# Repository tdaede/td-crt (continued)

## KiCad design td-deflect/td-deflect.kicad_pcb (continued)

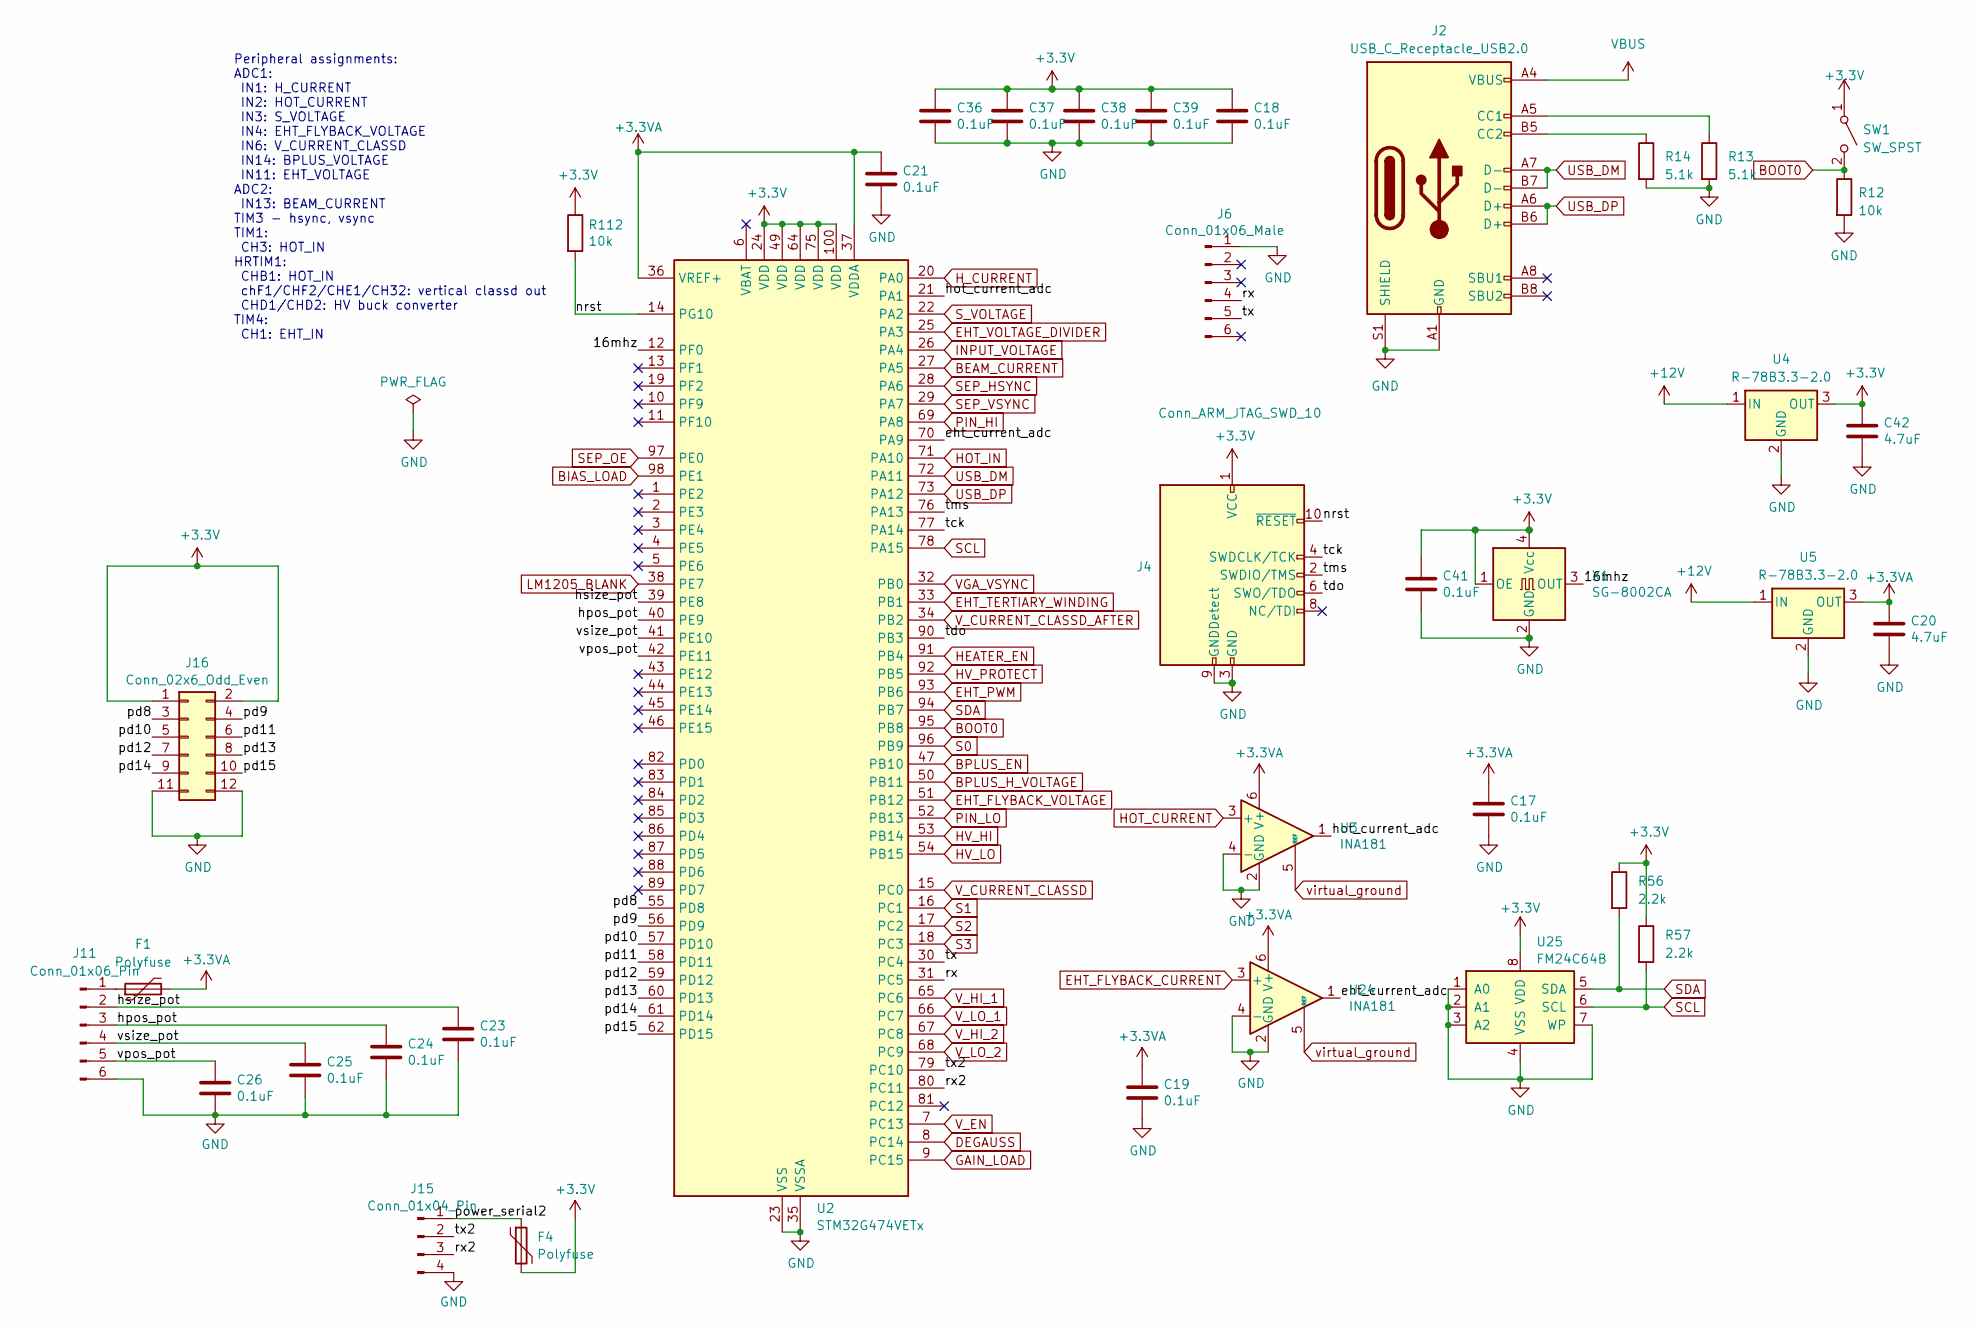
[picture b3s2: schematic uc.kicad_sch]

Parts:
C17, C18, C19, C21, C23, C24, C25, C26, C36, C37, C38, C39, C41: 0.1uF; C_0805_2012Metric_Pad1.18x1.45mm_HandSolder; Voltage 10V; Digikey 311-1140-1-ND
C20, C42: 4.7uF; C_1206_3216Metric; Voltage 10V; Digikey 1276-3177-1-ND
F1: Polyfuse; Fuse_0805_2012Metric; Digikey 507-1801-1-ND
F4: Polyfuse; Fuse_1206_3216Metric; Digikey 507-1801-1-ND
J2: USB_C_Receptacle_USB2.0; USB_C_Receptacle_XKB_U262-16XN-4BVC11; Digikey 2073-USB4105-GF-ACT-ND
J4: Conn_ARM_JTAG_SWD_10; PinHeader_2x05_P1.27mm_Vertical_SMD; Digikey SAM9438-ND
J6: Conn_01x06_Male; PinHeader_1x06_P2.54mm_Vertical; Digikey DNP
J11: Conn_01x06_Pin; JST_XH_B6B-XH-A_1x06_P2.50mm_Vertical; Digikey 455-B6B-XH-A-ND
J15: Conn_01x04_Pin; JST_XH_B4B-XH-A_1x04_P2.50mm_Vertical; Digikey 455-B4B-XH-A-ND
J16: Conn_02x6_Odd_Even; IDC-Header_2x06_P2.54mm_Vertical; Digikey 2057-BHR-12-VUA-ND
R12: 10k; R_0805_2012Metric; Digikey 311-10.0KCRCT-ND
R13, R14: 5.1k; R_0805_2012Metric; Digikey 311-5.10KCRCT-ND
R56, R57: 2.2k; R_0805_2012Metric; Digikey 311-2.20KCRCT-ND
R112: 10k; R_0805_2012Metric_Pad1.20x1.40mm_HandSolder; Digikey 311-10.0KCRCT-ND
SW1: SW_SPST; SW_DPDT_CK_JS202011JCQN; Digikey CKN10723CT-ND
U2: STM32G474VETx; LQFP-100_14x14mm_P0.5mm; Digikey 497-19476-ND
U3, U24: INA181; SOT-23-6; Digikey 296-47658-1-ND
U4, U5: R-78B3.3-2.0; Converter_DCDC_RECOM_R-78B-2.0_THT; Digikey 945-3040-ND
U25: FM24C64B; SOIC-8_3.9x4.9mm_P1.27mm; Digikey 448-FM24C64B-GTRCT-ND
X1: SG-8002CA; Oscillator_SMD_SeikoEpson_SG8002CA-4Pin_7.0x5.0mm; Digikey CTX270LVCT-ND

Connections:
+3.3V: C18.1, C36.1, C37.1, C38.1, C39.1, C41.1, C42.1, F4.2, J4.1 (VCC), J16.1, J16.2, R56.1, R57.1, R112.1, SW1.1 (A), U2.24 (VDD), U2.49 (VDD), U2.64 (VDD), U2.75 (VDD), U2.100 (VDD), U4.3 (OUT), U25.8 (VDD), X1.1 (OE), X1.4 (Vcc)
+3.3VA: C17.1, C19.1, C20.1, C21.1, F1.2, U2.36 (VREF+), U2.37 (VDDA), U3.6 (V+), U5.3 (OUT), U24.6 (V+); also elsewhere on the board
+12V: U4.1 (IN), U5.1 (IN); also elsewhere on the board
/uc/16mhz: U2.12 (PF0), X1.3 (OUT)
/uc/eht_current_adc: U2.70 (PA9), U24.1
/uc/hot_current_adc: U2.21 (PA1), U3.1
/uc/hpos_pot: C24.1, J11.3, U2.40 (PE9)
/uc/hsize_pot: C23.1, J11.2, U2.39 (PE8)
/uc/nrst: J4.10 (~RESET), R112.2, U2.14 (PG10)
/uc/pd8: J16.3, U2.55 (PD8)
/uc/pd9: J16.4, U2.56 (PD9)
/uc/pd10: J16.5, U2.57 (PD10)
/uc/pd11: J16.6, U2.58 (PD11)
/uc/pd12: J16.7, U2.59 (PD12)
/uc/pd13: J16.8, U2.60 (PD13)
/uc/pd14: J16.9, U2.61 (PD14)
/uc/pd15: J16.10, U2.62 (PD15)
/uc/power_serial2: F4.1, J15.1
/uc/rx: J6.4, U2.31 (PC5)
/uc/rx2: J15.3, U2.80 (PC11)
/uc/tck: J4.4 (SWDCLK/TCK), U2.77 (PA14)
/uc/tdo: J4.6 (SWO/TDO), U2.90 (PB3)
/uc/tms: J4.2 (SWDIO/TMS), U2.76 (PA13)
/uc/tx: J6.5, U2.30 (PC4)
/uc/tx2: J15.2, U2.79 (PC10)
/uc/vpos_pot: C26.1, J11.5, U2.42 (PE11)
/uc/vsize_pot: C25.1, J11.4, U2.41 (PE10)
BEAM_CURRENT: U2.27 (PA5); also elsewhere on the board
BIAS_LOAD: U2.98 (PE1); also elsewhere on the board
BOOT0: R12.1, SW1.2 (B), U2.95 (PB8)
BPLUS_EN: U2.47 (PB10); also elsewhere on the board
BPLUS_H_VOLTAGE: U2.50 (PB11); also elsewhere on the board
DEGAUSS: U2.8 (PC14); also elsewhere on the board
EHT_FLYBACK_CURRENT: U24.3 (+); also elsewhere on the board
EHT_FLYBACK_VOLTAGE: U2.51 (PB12); also elsewhere on the board
EHT_PWM: U2.93 (PB6); also elsewhere on the board
EHT_TERTIARY_WINDING: U2.33 (PB1); also elsewhere on the board
EHT_VOLTAGE_DIVIDER: U2.25 (PA3); also elsewhere on the board
GAIN_LOAD: U2.9 (PC15); also elsewhere on the board
GND: C17.2, C18.2, C19.2, C20.2, C21.2, C23.2, C24.2, C25.2, C26.2, C36.2, C37.2, C38.2, C39.2, C41.2, C42.2, J2.A1 (GND), J2.A12 (GND), J2.B1 (GND), J2.B12 (GND), J2.S1 (SHIELD), J4.3 (GND), J4.5 (GND), J4.9 (GNDDetect), J6.1, J11.6, J15.4, J16.11, J16.12, R12.2, R13.2, R14.2, U2.23 (VSS), U2.35 (VSSA), U2.48 (VSS), U2.63 (VSS), U2.74 (VSS), U2.99 (VSS), U3.2 (GND), U3.4 (-), U4.2 (GND), U5.2 (GND), U24.2 (GND), U24.4 (-), U25.1 (A0), U25.2 (A1), U25.3 (A2), U25.4 (VSS), U25.7 (WP), X1.2 (GND); also elsewhere on the board
HEATER_EN: U2.91 (PB4); also elsewhere on the board
HOT_CURRENT: U3.3 (+); also elsewhere on the board
HOT_IN: U2.71 (PA10); also elsewhere on the board
HV_HI: U2.53 (PB14); also elsewhere on the board
HV_LO: U2.54 (PB15); also elsewhere on the board
HV_PROTECT: U2.92 (PB5); also elsewhere on the board
H_CURRENT: U2.20 (PA0); also elsewhere on the board
INPUT_VOLTAGE: U2.26 (PA4); also elsewhere on the board
LM1205_BLANK: U2.38 (PE7); also elsewhere on the board
unnamed: J2.A5 (CC1), R13.1
unnamed: J2.B5 (CC2), R14.1
unnamed: F1.1, J11.1
PIN_HI: U2.69 (PA8); also elsewhere on the board
PIN_LO: U2.52 (PB13); also elsewhere on the board
S0: U2.96 (PB9); also elsewhere on the board
S1: U2.16 (PC1); also elsewhere on the board
S2: U2.17 (PC2); also elsewhere on the board
S3: U2.18 (PC3); also elsewhere on the board
SCL: R57.2, U2.78 (PA15), U25.6 (SCL); also elsewhere on the board
SDA: R56.2, U2.94 (PB7), U25.5 (SDA); also elsewhere on the board
SEP_HSYNC: U2.28 (PA6); also elsewhere on the board
SEP_OE: U2.97 (PE0); also elsewhere on the board
SEP_VSYNC: U2.29 (PA7); also elsewhere on the board
S_VOLTAGE: U2.22 (PA2); also elsewhere on the board
USB_DM: J2.A7 (D-), J2.B7 (D-), U2.72 (PA11)
USB_DP: J2.A6 (D+), J2.B6 (D+), U2.73 (PA12)
VBUS: J2.A4 (VBUS), J2.A9 (VBUS), J2.B4 (VBUS), J2.B9 (VBUS)
VGA_VSYNC: U2.32 (PB0); also elsewhere on the board
V_CURRENT_CLASSD: U2.15 (PC0); also elsewhere on the board
V_CURRENT_CLASSD_AFTER: U2.34 (PB2); also elsewhere on the board
V_EN: U2.7 (PC13)
V_HI_1: U2.65 (PC6); also elsewhere on the board
V_HI_2: U2.67 (PC8); also elsewhere on the board
V_LO_1: U2.66 (PC7); also elsewhere on the board
V_LO_2: U2.68 (PC9); also elsewhere on the board
virtual_ground: U3.5 (REF), U24.5 (REF); also elsewhere on the board

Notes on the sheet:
Peripheral assignments: ADC1: IN1: H_CURRENT IN2: HOT_CURRENT IN3: S_VOLTAGE IN4: EHT_FLYBACK_VOLTAGE IN6: V_CURRENT_CLASSD IN14: BPLUS_VOLTAGE IN11: EHT_VOLTAGE ADC2: IN13: BEAM_CURRENT TIM3 - hsync, vsync TIM1: CH3: HOT_IN HRTIM1: CHB1: HOT_IN chF1/CHF2/CHE1/CH32: vertical classd out CHD1/CHD2: H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

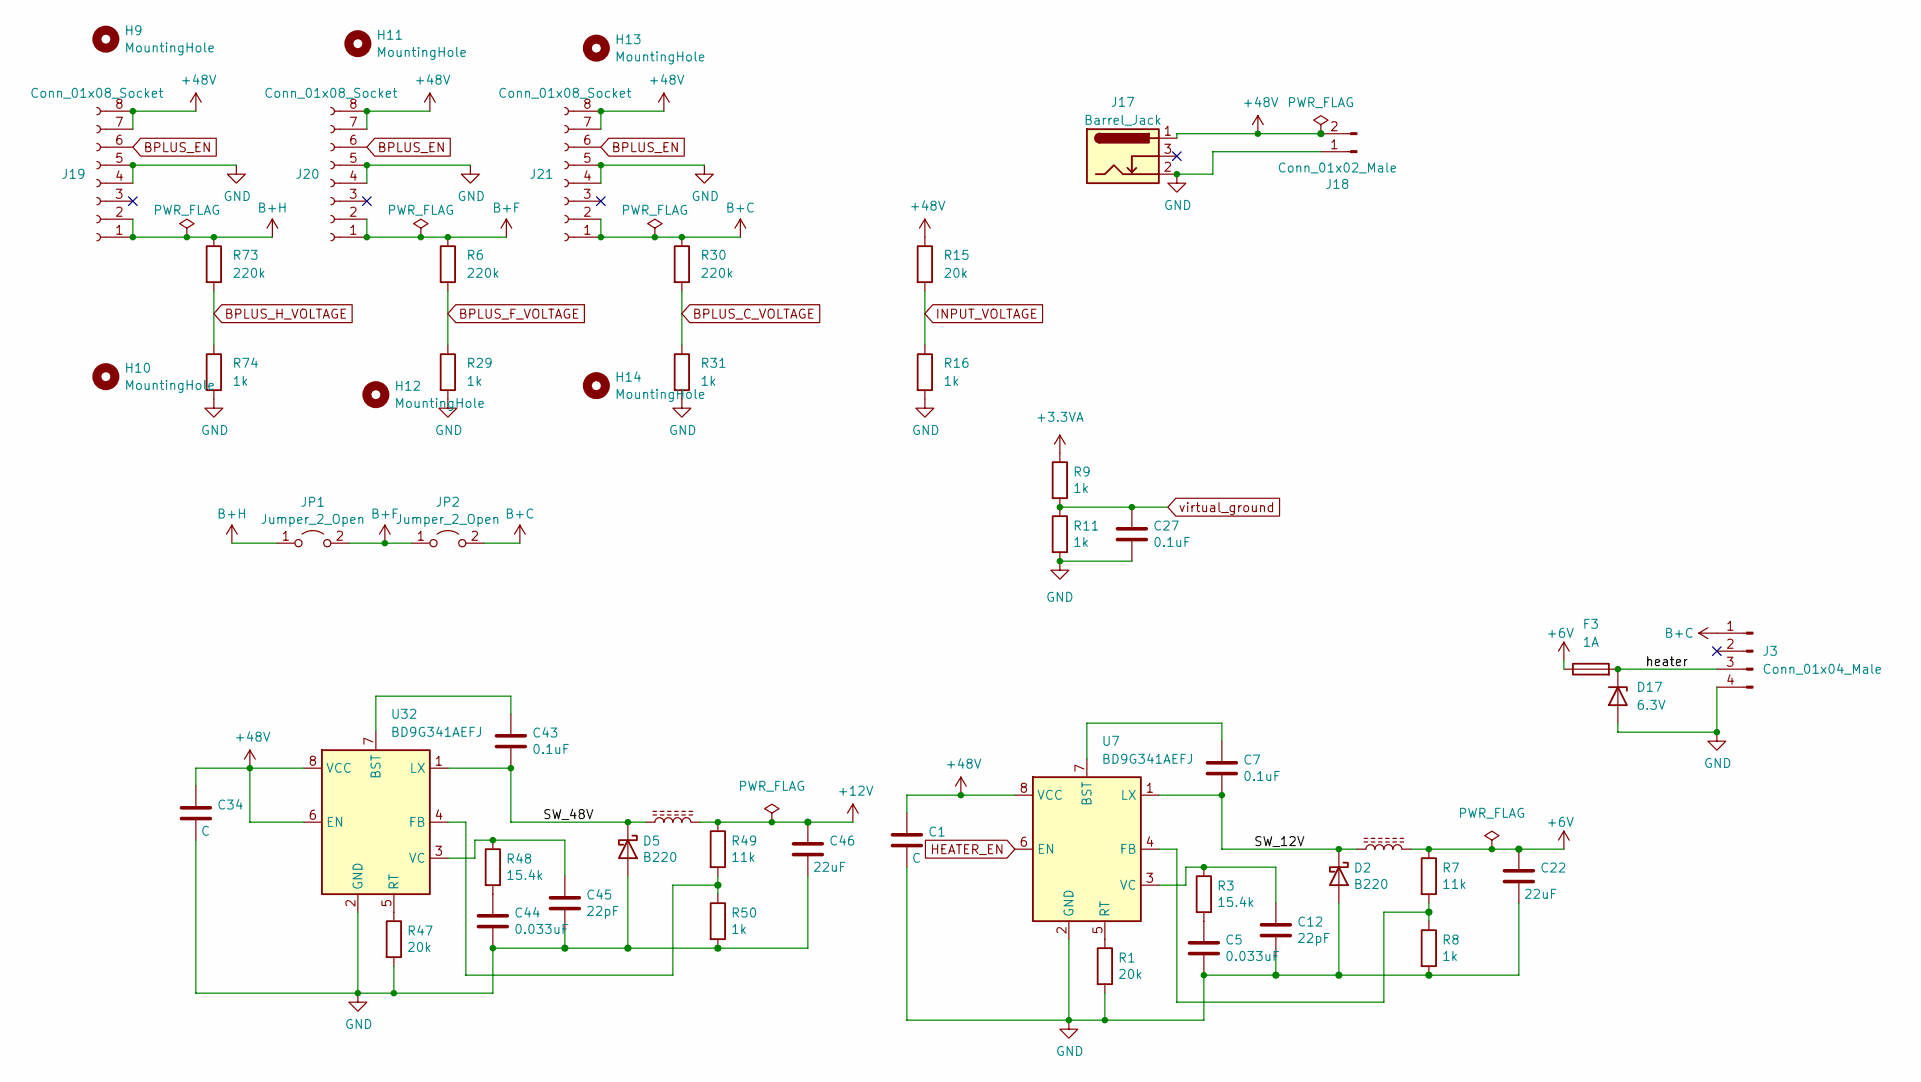
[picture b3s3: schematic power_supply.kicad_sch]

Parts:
C1, C34: C; C_1210_3225Metric; Voltage 50V; Digikey 587-1818-1-ND
C5, C44: 0.033uF; C_0805_2012Metric; Voltage 10V; Digikey 311-1374-1-ND
C7, C27, C43: 0.1uF; C_0805_2012Metric; Voltage 25V; Digikey 1276-1099-1-ND
C12, C45: 22pF; C_0805_2012Metric; Digikey 1276-2605-1-ND
C22, C46: 22uF; C_0805_2012Metric; Voltage 16V; Digikey 490-9956-1-ND
D2, D5: B220; D_SMB; Digikey B220A-FDICT-ND
D17: 6.3V; D_SMA; Digikey SMAJ6.5A-FDICT-ND
F3: 1A; Fuse_Schurter_UMT250; Digikey 486-3436-ND
H9, H10, H11, H12, H13, H14: MountingHole; MountingHole_3.2mm_M3; Digikey DNP
J3: Conn_01x04_Male; JST_XH_B4B-XH-A_1x04_P2.50mm_Vertical; Digikey 455-B4B-XH-A-ND
J17: Barrel_Jack; BarrelJack_Wuerth_6941xx301002; Digikey 732-5930-ND
J18: Conn_01x02_Male; PhoenixContact_MSTBVA_2,5_2-G_1x02_P5.00mm_Vertical; Digikey 277-1150-ND
J19, J20, J21: Conn_01x08_Socket; PinSocket_1x08_P2.54mm_Vertical; Digikey S7041-ND
JP1, JP2: Jumper_2_Open; PinHeader_1x02_P2.54mm_Vertical; Digikey DNP
L1, L5: 47uH; L_Bourns_SRR1260; Digikey SRF1260-470MCT-ND
R1, R47: 20k; R_0805_2012Metric; Digikey 311-20.0KCRCT-ND
R3, R48: 15.4k; R_0805_2012Metric; Digikey 311-15.4KCRCT-ND
R6, R30, R73: 220k; R_0805_2012Metric_Pad1.20x1.40mm_HandSolder; Digikey 311-220KCRCT-ND
R7, R49: 11k; R_0805_2012Metric; Digikey 311-11.0KCRCT-ND
R8, R9, R11, R50: 1k; R_0805_2012Metric; Digikey 311-1.00KCRCT-ND
R15: 20k; R_0805_2012Metric_Pad1.20x1.40mm_HandSolder; Digikey 311-20.0KCRCT-ND
R16, R29, R31, R74: 1k; R_0805_2012Metric_Pad1.20x1.40mm_HandSolder; Digikey 311-1.00KCRCT-ND
U7, U32: BD9G341AEFJ; SOIC-8-1EP_3.9x4.9mm_P1.27mm_EP2.41x3.3mm_ThermalVias; Digikey BD9G341AEFJ-E2CT-ND

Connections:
+3.3VA: R9.1; also elsewhere on the board
+6V: C22.1, F3.1, L1.2, R7.1
+12V: C46.1, L5.2, R49.1; also elsewhere on the board
+48V: C1.1, C34.1, J17.1, J18.2, J19.7, J19.8, J20.7, J20.8, J21.7, J21.8, R15.1, U7.8 (VCC), U32.6 (EN), U32.8 (VCC); also elsewhere on the board
/power_supply/SW_12V: C7.2, D2.1 (K), L1.1, U7.1 (LX)
/power_supply/SW_48V: C43.2, D5.1 (K), L5.1, U32.1 (LX)
/power_supply/heater: D17.1 (K), F3.2, J3.3
B+C: J3.1, J21.1, J21.2, JP2.2 (B), R30.1
B+F: J20.1, J20.2, JP1.2 (B), JP2.1 (A), R6.1; also elsewhere on the board
B+H: J19.1, J19.2, JP1.1 (A), R73.1; also elsewhere on the board
BPLUS_C_VOLTAGE: R30.2, R31.1
BPLUS_EN: J19.6, J20.6, J21.6; also elsewhere on the board
BPLUS_F_VOLTAGE: R6.2, R29.1
BPLUS_H_VOLTAGE: R73.2, R74.1; also elsewhere on the board
GND: C1.2, C5.2, C12.2, C22.2, C27.2, C34.2, C44.2, C45.2, C46.2, D2.2 (A), D5.2 (A), D17.2 (A), J3.4, J17.2, J18.1, J19.4, J19.5, J20.4, J20.5, J21.4, J21.5, R1.2, R8.2, R11.2, R16.2, R29.2, R31.2, R47.2, R50.2, R74.2, U7.2 (GND), U7.9 (GND), U32.2 (GND), U32.9 (GND); also elsewhere on the board
HEATER_EN: U7.6 (EN); also elsewhere on the board
INPUT_VOLTAGE: R15.2, R16.1; also elsewhere on the board
unnamed: C5.1, R3.2
unnamed: C44.1, R48.2
unnamed: C7.1, U7.7 (BST)
unnamed: R7.2, R8.1, U7.4 (FB)
unnamed: R1.1, U7.5 (RT)
unnamed: C12.1, R3.1, U7.3 (VC)
unnamed: C43.1, U32.7 (BST)
unnamed: R49.2, R50.1, U32.4 (FB)
unnamed: R47.1, U32.5 (RT)
unnamed: C45.1, R48.1, U32.3 (VC)
virtual_ground: C27.1, R9.2, R11.1; also elsewhere on the board

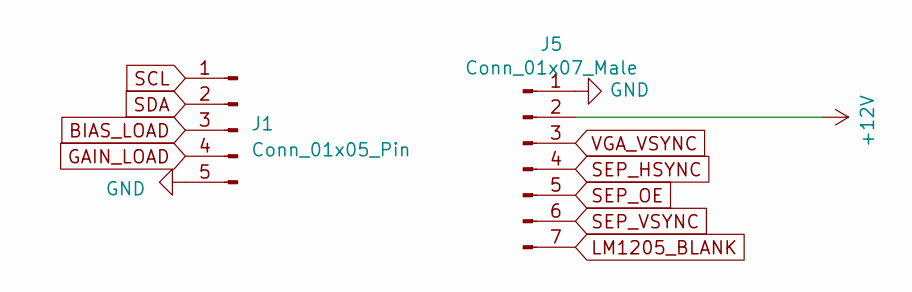
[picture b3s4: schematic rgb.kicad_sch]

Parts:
J1: Conn_01x05_Pin; JST_XH_B5B-XH-A_1x05_P2.50mm_Vertical; Digikey 455-B5B-XH-A-ND
J5: Conn_01x07_Male; JST_XH_B7B-XH-A_1x07_P2.50mm_Vertical; Digikey 1175-51025-07-0100-01-ND

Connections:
+12V: J5.2; also elsewhere on the board
BIAS_LOAD: J1.3; also elsewhere on the board
GAIN_LOAD: J1.4; also elsewhere on the board
GND: J1.5, J5.1; also elsewhere on the board
LM1205_BLANK: J5.7; also elsewhere on the board
SCL: J1.1; also elsewhere on the board
SDA: J1.2; also elsewhere on the board
SEP_HSYNC: J5.4; also elsewhere on the board
SEP_OE: J5.5; also elsewhere on the board
SEP_VSYNC: J5.6; also elsewhere on the board
VGA_VSYNC: J5.3; also elsewhere on the board

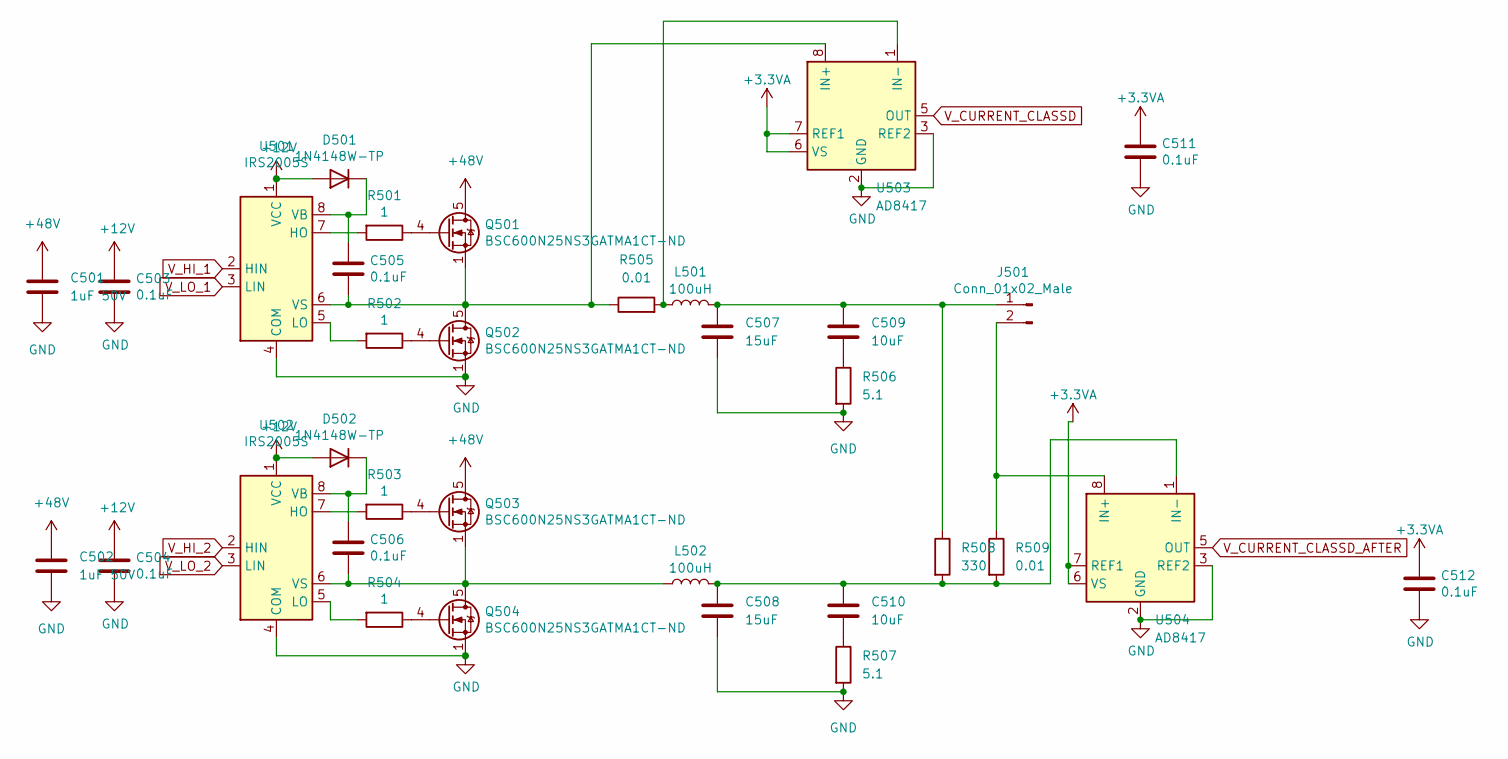
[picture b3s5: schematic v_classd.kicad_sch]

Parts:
C501, C502: 1uF 50V; C_0805_2012Metric_Pad1.18x1.45mm_HandSolder; Digikey 13-CC0805KFX7R9BB105CT-ND
C503, C504, C505, C506, C511, C512: 0.1uF; C_0805_2012Metric_Pad1.18x1.45mm_HandSolder; Digikey 311-1140-1-ND
C507, C508: 15uF; C_Elec_6.3x7.7; Digikey 565-HHXD500ARA150MF80GCT-ND
C509, C510: 10uF; C_Elec_6.3x5.8; Digikey 565-4781-1-ND
D501, D502: 1N4148W-TP; D_SOD-123; Digikey 1N4148WTPMSCT-ND
J501: Conn_01x02_Male; sony_monitor_2p; Digikey DNP
L501, L502: 100uH; L_Bourns_SRR1260; Digikey 4044-CSAB1260A-101MCT-ND
Q501, Q502, Q503, Q504: BSC600N25NS3GATMA1CT-ND; TDSON-8-1; Digikey BSC600N25NS3GATMA1CT-ND
R501, R502, R503, R504: 1; R_0805_2012Metric_Pad1.20x1.40mm_HandSolder; Digikey 311-1.00CRCT-ND
R505, R509: 0.01; R_0805_2012Metric_Pad1.20x1.40mm_HandSolder; Digikey 311-0.01NUCT-ND
R506, R507: 5.1; R_0805_2012Metric_Pad1.20x1.40mm_HandSolder; Digikey 311-5.1ARCT-ND
R508: 330; R_0805_2012Metric_Pad1.20x1.40mm_HandSolder; Digikey 13-RC0805FR-13330RLCT-ND
U501, U502: IRS2005S; SOIC-8_3.9x4.9mm_P1.27mm; Digikey IRS2005STRPBFCT-ND
U503, U504: AD8417; SOIC-8_3.9x4.9mm_P1.27mm; Digikey 505-AD8417WBRZ-ND

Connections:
+3.3VA: C511.1, C512.1, U503.6 (VS), U503.7 (REF1), U504.6 (VS), U504.7 (REF1); also elsewhere on the board
+12V: C503.1, C504.1, D501.2 (A), D502.2 (A), U501.1 (VCC), U502.1 (VCC); also elsewhere on the board
+48V: C501.1, C502.1, Q501.5 (D), Q503.5 (D); also elsewhere on the board
GND: C501.2, C502.2, C503.2, C504.2, C507.2, C508.2, C511.2, C512.2, Q502.1 (S), Q502.2 (S), Q502.3 (S), Q504.1 (S), Q504.2 (S), Q504.3 (S), R506.2, R507.2, U501.4 (COM), U502.4 (COM), U503.2 (GND), U503.3 (REF2), U504.2 (GND), U504.3 (REF2); also elsewhere on the board
unnamed: C509.2, R506.1
unnamed: C510.2, R507.1
unnamed: C505.1, D501.1 (K), U501.8 (VB)
unnamed: C506.1, D502.1 (K), U502.8 (VB)
unnamed: C507.1, C509.1, J501.1, L501.2, R508.1
unnamed: J501.2, R509.1, U504.8 (IN+)
unnamed: Q501.4 (G), R501.1
unnamed: C505.2, Q501.1 (S), Q501.2 (S), Q501.3 (S), Q502.5 (D), R505.1, U501.6 (VS), U503.8 (IN+)
unnamed: Q502.4 (G), R502.1
unnamed: Q503.4 (G), R503.1
unnamed: C506.2, L502.1, Q503.1 (S), Q503.2 (S), Q503.3 (S), Q504.5 (D), U502.6 (VS)
unnamed: Q504.4 (G), R504.1
unnamed: R501.2, U501.7 (HO)
unnamed: R502.2, U501.5 (LO)
unnamed: R503.2, U502.7 (HO)
unnamed: R504.2, U502.5 (LO)
unnamed: L501.1, R505.2, U503.1 (IN-)
unnamed: C508.1, C510.1, L502.2, R508.2, R509.2, U504.1 (IN-)
V_CURRENT_CLASSD: U503.5 (OUT); also elsewhere on the board
V_CURRENT_CLASSD_AFTER: U504.5 (OUT); also elsewhere on the board
V_HI_1: U501.2 (HIN); also elsewhere on the board
V_HI_2: U502.2 (HIN); also elsewhere on the board
V_LO_1: U501.3 (LIN); also elsewhere on the board
V_LO_2: U502.3 (LIN); also elsewhere on the board

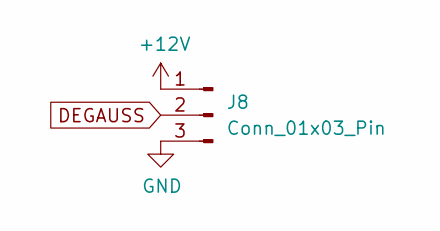
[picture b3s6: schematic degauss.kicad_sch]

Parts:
J8: Conn_01x03_Pin; JST_XH_B3B-XH-A_1x03_P2.50mm_Vertical; Digikey 455-2248-ND

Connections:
+12V: J8.1; also elsewhere on the board
DEGAUSS: J8.2; also elsewhere on the board
GND: J8.3; also elsewhere on the board

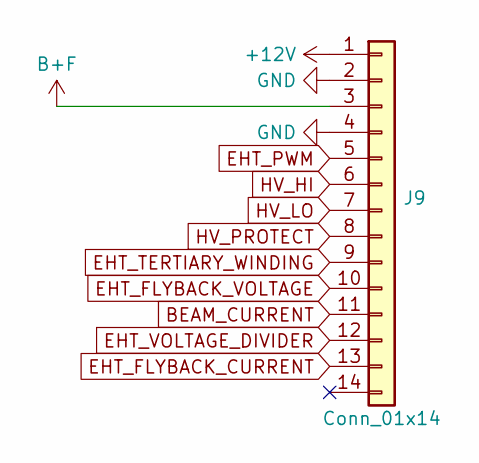
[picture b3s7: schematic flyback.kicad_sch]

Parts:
J9: Conn_01x14; JST_XH_B14B-XH-A_1x14_P2.50mm_Vertical; Digikey 455-B14B-XH-A-ND

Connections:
+12V: J9.1; also elsewhere on the board
B+F: J9.3; also elsewhere on the board
BEAM_CURRENT: J9.11; also elsewhere on the board
EHT_FLYBACK_CURRENT: J9.13; also elsewhere on the board
EHT_FLYBACK_VOLTAGE: J9.10; also elsewhere on the board
EHT_PWM: J9.5; also elsewhere on the board
EHT_TERTIARY_WINDING: J9.9; also elsewhere on the board
EHT_VOLTAGE_DIVIDER: J9.12; also elsewhere on the board
GND: J9.2, J9.4; also elsewhere on the board
HV_HI: J9.6; also elsewhere on the board
HV_LO: J9.7; also elsewhere on the board
HV_PROTECT: J9.8; also elsewhere on the board

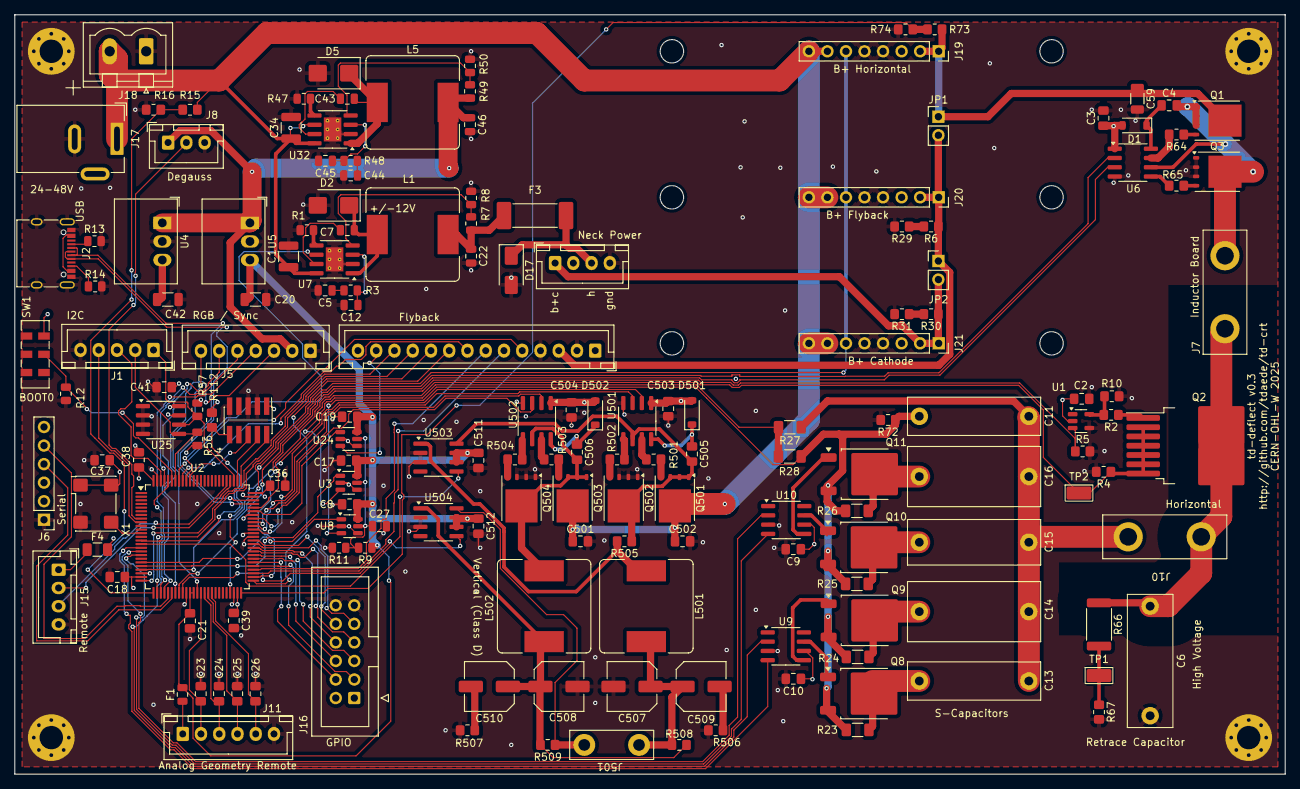
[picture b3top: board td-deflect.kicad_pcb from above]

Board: 4 copper layers, 174.0 x 104.0 mm, 175 parts (0 on the bottom side), 133 nets.

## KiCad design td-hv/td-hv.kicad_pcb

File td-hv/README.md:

**td-hv** is a HV/EHT driver board. It uses a K7000 clone replacement flyback (053X0528-001).

The circuit is a classic current mode flyback driver circuit based on the UCC3801. The circuit integrates secondary-side feedback by (ab)using the resistive divider created by the focus and screen potentiometers of the flyback, inspired by the drive circuit on the MS-2931 and similar monitors.

The primary drive transistor is a SiC MOSFET which has a sufficiently low gate drive voltage to be driven directly by the 12V gate drive output of the UCC3801.

The circuit free-runs at 14kHz, but can by synchronized to a higher frequency with a sync input pin, which is critical for not having a jittery iamge.

The circuit is currently very unstable. The primary problem is that the enormous amount of leakage inductance and capacitance of the flyback causes very slow ringing of the primary current. If the duty cycle and frequency of the switching circuit turn on the MOSFET while the switching node is at a high voltage (e.g. more than 100V) the sudden amount of current produces a voltage spike that confuses the current mode sensing of the UCC3801. Series LR damping has proven only marginally effective.

There is also an X-Ray protection circuit which provides a redundant shutdown path by measuring the peak voltage off a tertiary winding of the flyback.

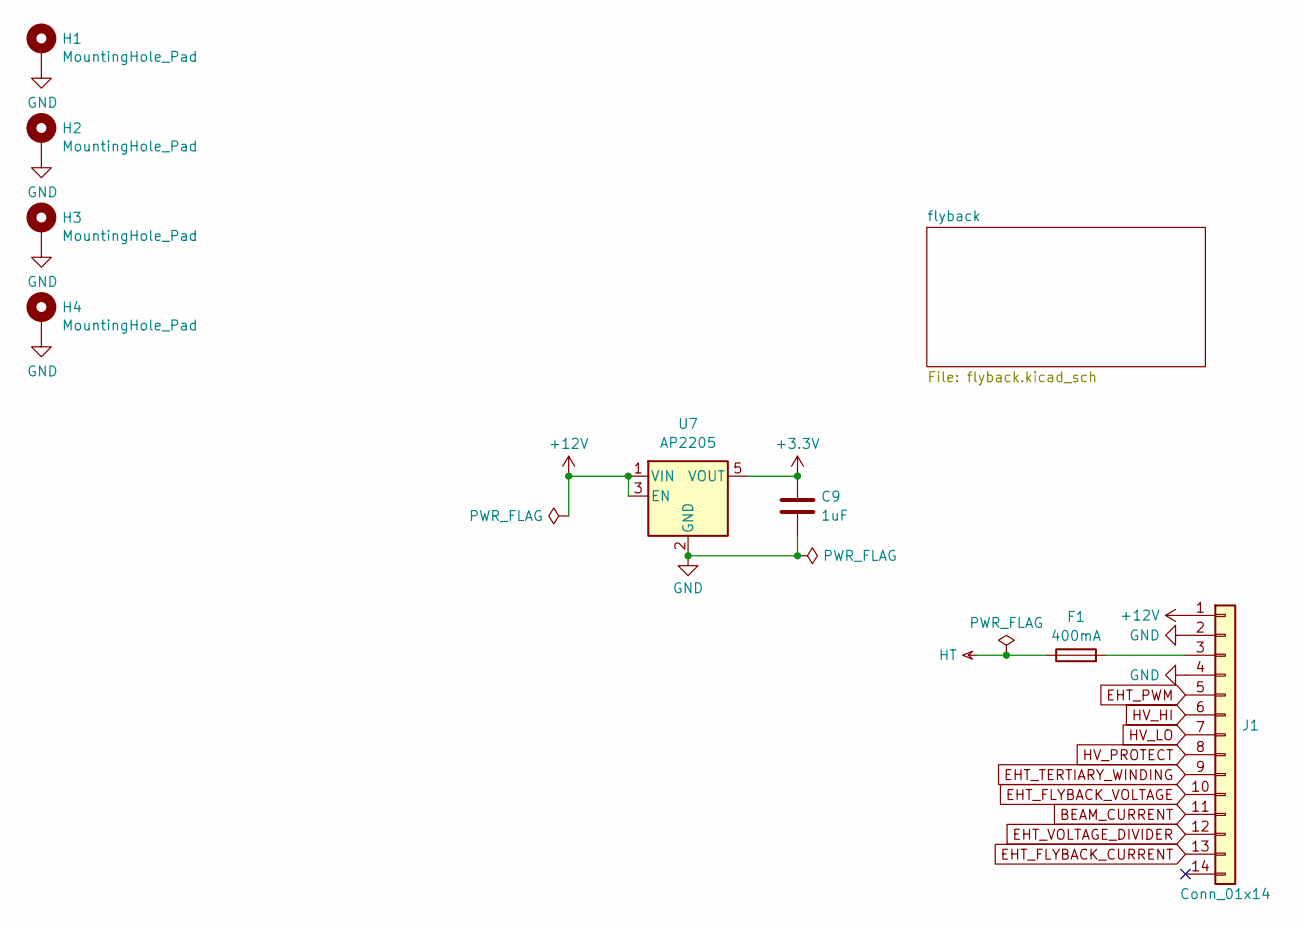
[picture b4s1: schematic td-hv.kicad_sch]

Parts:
C9: 1uF; C_0805_2012Metric; Digikey 311-1365-1-ND
F1: 400mA; Fuse_Schurter_UMZ250; Digikey 486-4326-ND
H1, H2, H3, H4: MountingHole_Pad; MountingHole_3.2mm_M3_Pad_Via; Digikey DNP
J1: Conn_01x14; JST_XH_B14B-XH-A_1x14_P2.50mm_Vertical; Digikey 455-B14B-XH-A-ND
U7: AP2205; SOT-23-5; Digikey 31-AP2205-33W5-7CT-ND

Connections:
+3.3V: C9.1, U7.5 (VOUT); also elsewhere on the board
+12V: J1.1, U7.1 (VIN), U7.3 (EN); also elsewhere on the board
BEAM_CURRENT: J1.11; also elsewhere on the board
EHT_FLYBACK_CURRENT: J1.13; also elsewhere on the board
EHT_FLYBACK_VOLTAGE: J1.10; also elsewhere on the board
EHT_PWM: J1.5; also elsewhere on the board
EHT_TERTIARY_WINDING: J1.9; also elsewhere on the board
EHT_VOLTAGE_DIVIDER: J1.12; also elsewhere on the board
GND: C9.2, H1.1, H2.1, H3.1, H4.1, J1.2, J1.4, U7.2 (GND); also elsewhere on the board
HT: F1.1; also elsewhere on the board
HV_HI: J1.6; also elsewhere on the board
HV_LO: J1.7; also elsewhere on the board
HV_PROTECT: J1.8; also elsewhere on the board
unnamed: F1.2, J1.3

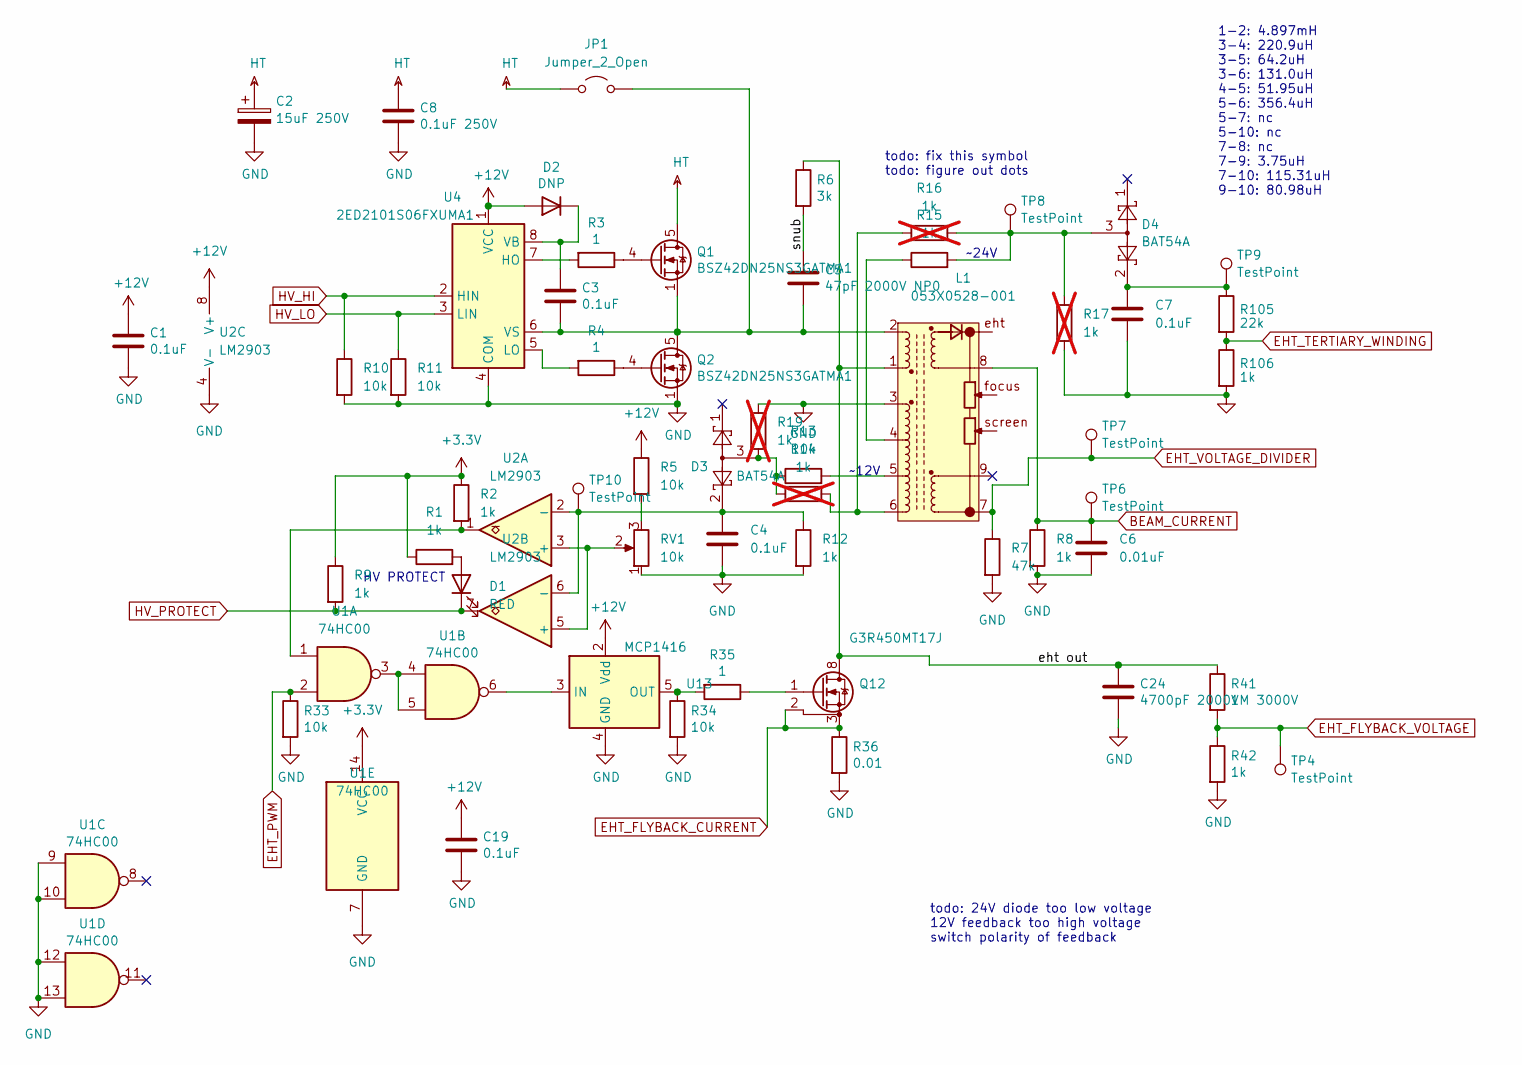
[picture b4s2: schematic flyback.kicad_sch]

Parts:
C1, C3, C4, C7, C19: 0.1uF; C_0805_2012Metric; Digikey 1276-1099-1-ND
C2: 15uF 250V; CP_Elec_10x10.5; Digikey 493-6738-1-ND
C5: 47pF 2000V NP0; C_1812_4532Metric; Digikey 478-3005-1-ND
C6: 0.01uF; C_0805_2012Metric; Digikey 311-1136-1-ND
C8: 0.1uF 250V; C_1206_3216Metric; Digikey 445-8899-1-ND
C24: 4700pF 2000V; C_Rect_L18.0mm_W5.0mm_P15.00mm_FKS3_FKP3; Voltage 2000V; Digikey 495-3227-ND
D1: RED; LED_0805_2012Metric; Digikey 350-2039-1-ND
D2: DNP; D_SMA; Digikey ES1G-FDICT-ND
D3, D4: BAT54A; SOT-23; Digikey 1655-BAT54ACT-ND
JP1: Jumper_2_Open; PinHeader_1x02_P2.54mm_Vertical
L1: 053X0528-001; Digikey DNP
Q1, Q2: BSZ42DN25NS3GATMA1; TDSON-8-1; Digikey BSZ42DN25NS3GATMA1CT-ND
Q12: G3R450MT17J; TO-263-7_TabPin8_GeneSiC; Digikey 1242-G3R450MT17J-ND
R1, R2, R8, R9, R42, R106: 1k; R_0805_2012Metric; Digikey 311-1.00KCRCT-ND
R3, R4, R35: 1; R_0805_2012Metric; Digikey 311-1.00CRCT-ND
R5, R10, R11, R33, R34: 10k; R_0805_2012Metric; Digikey 311-1.00KCRCT-ND
R6: 3k; R_2512_6332Metric; Digikey 13-RC2512FK-073KLCT-ND
R7: 47k; R_0805_2012Metric; Digikey 311-47.0KCRCT-ND
R12, R15: 1k; R_0805_2012Metric
R13: 10k; R_0805_2012Metric
R14, R16, R17, R19: 1k; R_0805_2012Metric; not fitted
R36: 0.01; R_0805_2012Metric; Digikey 311-0.01NUCT-ND
R41: 1M 3000V; R_2512_6332Metric; Digikey CHV2512-FX-1004ELFCT-ND
R105: 22k; R_0805_2012Metric; Digikey 311-22.0KCRCT-ND
RV1: 10k; Potentiometer_Bourns_3314G_Vertical; Digikey 563-ST4ETB103CT-ND
TP4, TP6, TP7, TP8, TP9, TP10: TestPoint; TestPoint_Keystone_5019_Miniature; Digikey 36-5019CT-ND
U1: 74HC00; SOIC-14_3.9x8.7mm_P1.27mm; Digikey 1727-2773-1-ND
U2: LM2903; SOIC-8_3.9x4.9mm_P1.27mm; Digikey LM2903QS-13DICT-ND
U4: 2ED2101S06FXUMA1; SOIC-8_3.9x4.9mm_P1.27mm; Digikey 448-2ED2101S06FXUMA1CT-ND
U13: MCP1416; SOT-23-5; Digikey MCP1416T-E/OTCT-ND

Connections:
+3.3V: R1.1, R2.1, R9.1, U1.14 (VCC); also elsewhere on the board
+12V: C1.1, C19.1, D2.2 (A), R5.1, U2.8 (V+), U4.1 (VCC), U13.2 (Vdd); also elsewhere on the board
/flyback/eht out: C24.1, L1.1, Q12.8 (D), R6.1, R41.1
/flyback/snub: C5.1, R6.2
BEAM_CURRENT: C6.1, L1.8, R8.1, TP6.1; also elsewhere on the board
EHT_FLYBACK_CURRENT: Q12.2 (DS), Q12.3 (S), Q12.4 (S), Q12.5 (S), Q12.6 (S), Q12.7 (S), R36.1; also elsewhere on the board
EHT_FLYBACK_VOLTAGE: R41.2, R42.1, TP4.1; also elsewhere on the board
EHT_PWM: R33.1, U1.2; also elsewhere on the board
EHT_TERTIARY_WINDING: R105.2, R106.1; also elsewhere on the board
EHT_VOLTAGE_DIVIDER: L1.7, R7.1, TP7.1; also elsewhere on the board
GND: C1.2, C2.2, C4.2, C6.2, C7.2, C8.2, C19.2, C24.2, L1.3, Q2.1 (S), Q2.2 (S), Q2.3 (S), R7.2, R8.2, R10.2, R11.2, R12.2, R17.1, R19.2, R33.2, R34.2, R36.2, R42.2, R106.2, RV1.1, U1.7 (GND), U1.9, U1.10, U1.12, U1.13, U2.4 (V-), U4.4 (COM), U13.4 (GND); also elsewhere on the board
HT: C2.1, C8.1, JP1.1 (A), Q1.5 (D); also elsewhere on the board
HV_HI: R10.1, U4.2 (HIN); also elsewhere on the board
HV_LO: R11.1, U4.3 (LIN); also elsewhere on the board
HV_PROTECT: D1.1 (K), R9.2, U2.7; also elsewhere on the board
unnamed: C7.1, D4.2, R105.1, TP9.1
unnamed: D1.2 (A), R1.2
unnamed: C3.1, D2.1 (K), U4.8 (VB)
unnamed: D3.3, R13.1, R14.1, R19.1
unnamed: D4.3, R15.2, R16.2, R17.2, TP8.1
unnamed: C3.2, C5.2, JP1.2 (B), L1.2, Q1.1 (S), Q1.2 (S), Q1.3 (S), Q2.5 (D), U4.6 (VS)
unnamed: L1.4, R15.1
unnamed: L1.5, R13.2
unnamed: L1.6, R14.2, R16.1
unnamed: Q1.4 (G), R3.1
unnamed: Q2.4 (G), R4.1
unnamed: Q12.1 (G), R35.1
unnamed: R2.2, U1.1, U2.1
unnamed: R5.2, RV1.3
unnamed: U1.3, U1.4, U1.5
unnamed: RV1.2, U2.3 (+), U2.5 (+)
unnamed: C4.1, D3.2, R12.1, TP10.1, U2.2 (-), U2.6 (-)
unnamed: R3.2, U4.7 (HO)
unnamed: R4.2, U4.5 (LO)
unnamed: U1.6, U13.3 (IN)
unnamed: R34.1, R35.2, U13.5 (OUT)

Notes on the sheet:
~24V
~12V
todo: 24V diode too low voltage 12V feedback too high voltage switch polarity of feedback
1-2: 4.897mH 3-4: 220.9uH 3-5: 64.2uH 3-6: 131.0uH 4-5: 51.95uH 5-6: 356.4uH 5-7: nc 5-10: nc 7-8: nc 7-9: 3.75uH 7-10: 115.31uH 9-10: 80.98uH
todo: fix this symbol todo: figure out dots
HV PROTECT
